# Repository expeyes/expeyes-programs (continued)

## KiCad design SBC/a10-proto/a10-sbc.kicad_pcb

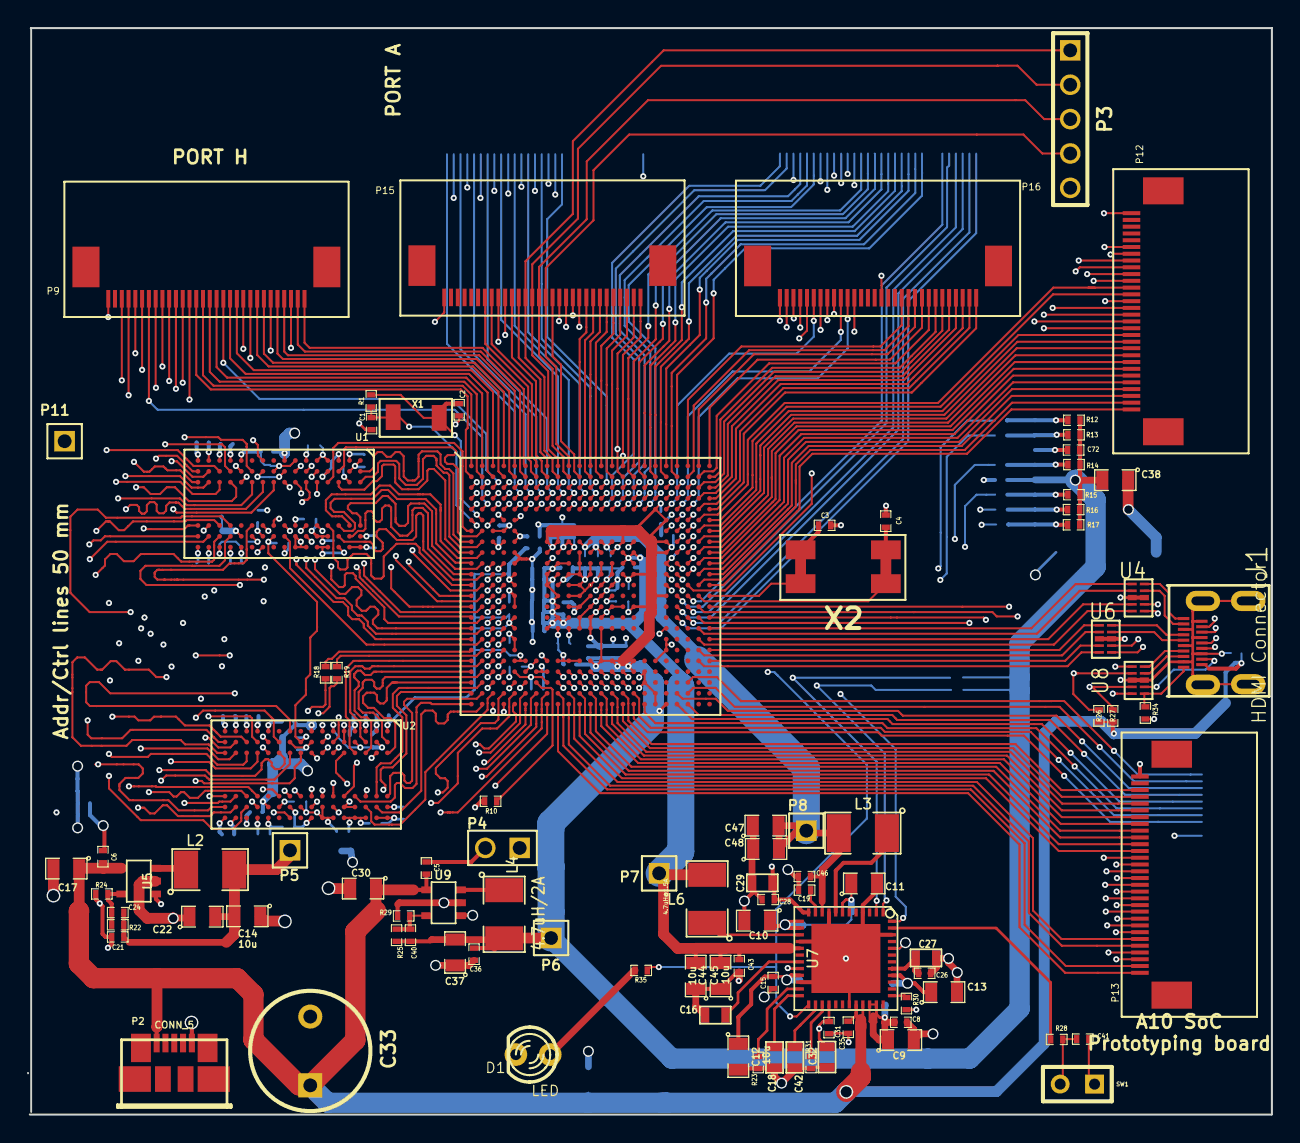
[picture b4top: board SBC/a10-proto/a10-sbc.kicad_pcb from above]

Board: 6 copper layers, 91.8 x 80.3 mm, 180 parts (0 on the bottom side), 331 nets.

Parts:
C1, C2, C3, C4: 18pF; SM0402
C5, C6, C24, C40: 22pF; SM0402
C7, C8, C15, C19, C21, C23, C26, C28, C31, C35, C36, C41, C43, C46, C49, C50, C51, C52, C53, C54, C55, C56, C57, C58, C59, C60, C61, C62, C63, C64, C65, C66, C67, C68, C69, C70, C71, C72, C73, C74, C75, C76, C77, C78, C79, C80, C81, C82, C83, C84, C85, C86, C87, C88, C89, C90, C91, C92, C93, C94, C95, C96, C97, C98, C99, C100, C101, C102, C103, C104, C105, C106, C107, C109, C110, C111, C112: .22u; SM0402
C9, C10, C11, C12, C13, C14, C17, C22, C30, C34, C37, C38, C44, C45, C47, C48: 10u; SM0805
C16, C18, C42: 1uF; SM0603
C20, C27, C29: 4.7u; SM0603
C32: 1u; SM0603
C33: 220u; C2V8
C108: 22u; SM0402
D1: LED; LED-3MM
J1: HDMI Connector; HDMI
J5: USD; microsd_socket
L2: 4.7uH/3A; SM1210L
L3, L6: 4.7uH@1.5A; SM1210L
L4: 4.7uH/2A; SM1210L
P1, P9, P10, P12, P13, P15, P16: C30; FPC30-0.5mm
P2: CONN_5; conn_usb_B_micro_smd
P3: CONN_5; PIN_ARRAY_5x1
P4: UBOOT; PIN_ARRAY_2X1
P5, P6, P7, P8, P11: CONN_1; PIN_ARRAY_1
P14: CONN_10; FPC10-0.5mm
R1: 10M; SM0402
R2: 5k1; SM0402
R3, R5, R6, R7, R8, R9, R28: 33; SM0402
R4, R10, R11, R30: 240; SM0402
R12, R13, R14, R15, R16, R17: 47K; SM0402
R18, R19: 22; SM0402
R20, R21, R26, R27, R31, R32, R33: 2k2; SM0402
R22, R25: 15k; SM0402
R23: 200k; SM0402
R24: 10k; SM0402
R29: 3.3k; SM0402
R34: 47k; SM0402
R35: 4k7; SM0402
SW1: SW_PUSH; SIL-2
U1, U2: 4GBDDR3; FBGA96-new
U3: A10-SOC; TFBGA441-new
U4, U6, U8: 524P; RCLAMP
U5, U9: SY8008C; SOT23-5
U7: AXP209; QFN48+1
X1: 32.768k; crystal-32k-4.5x1.9mm
X2: 24MHz; Crystal_SMD_7x5mm

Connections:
1.2V: C43.1, C44.2, C45.2, C49.1, C50.1, C51.1, C52.1, C53.1, C54.1, C55.1, C56.1, L6.2, P7.1, U3.J15, U3.J16, U3.K9, U3.K10, U3.K15, U3.K16, U3.L8, U3.L9, U3.M8, U3.N9, U3.P9, U3.R9, U3.R10, U3.T8, U7.17
1.25V: C46.1, C47.2, C48.2, C57.1, C58.1, C59.1, L3.2, P8.1, U3.H11, U3.H12, U3.H13, U3.H14, U3.J12, U3.J13, U7.10
3.3V: C7.2, C36.2, C37.2, C38.2, C40.2, C60.1, C61.1, C62.1, C63.1, C64.1, C65.1, C66.1, C67.1, C68.1, C69.1, C70.1, C71.1, C72.1, J5.4, L4.2, P6.1, R12.1, R13.1, R14.1, R15.1, R16.1, R17.1, R20.1, R21.1, R25.2, U3.AC19, U3.E18, U3.F19, U3.H8, U3.H9, U3.H10, U3.H15, U3.H19, U3.J8, U3.J9, U3.J10, U3.J14, U3.J19, U3.L15, U3.L16, U3.N19, U3.P16, U3.T13, U3.W12, U3.W13, U3.W14, U3.W15, U3.W16, U3.Y16
5V_IN: C5.2, C6.2, C17.1, C23.2, C30.1, C33.1, C34.1, C35.2, J1.18, P2.1, R26.1, R27.1, U5.4, U7.32, U7.33, U9.4
/BA0: U1.M2, U2.M2, U3.K3
/BA1: U1.N8, U2.N8, U3.L4
/BA2: U1.M3, U2.M3, U3.K4
/CK: R18.1, U1.J7, U2.J7
/CK#: R19.1, U1.K7, U2.K7
/CKE: U1.K9, U2.K9, U3.N3
/CS#: U1.L2, U2.L2, U3.V3
/DQ0: U2.E3, U3.AB4
/DQ1: U2.F7, U3.AC8
/DQ2: U2.F2, U3.AC4
/DQ3: U2.F8, U3.AB8
/DQ4: U2.H7, U3.AC7
/DQ5: U2.H8, U3.AB5
/DQ6: U2.H3, U3.AB7
/DQ7: U2.G2, U3.AC3
/DQ8: U2.A7, U3.AB2
/DQ9: U2.C3, U3.Y1
/DQ10: U2.B8, U3.AC2
/DQ11: U2.A2, U3.Y2
/DQ12: U2.A3, U3.AA1
/DQ13: U2.C8, U3.AB3
/DQ14: U2.C2, U3.W2
/DQ15: U2.D7, U3.AC1
/DQ16: U1.F2, U3.N1
/DQ17: U1.F7, U3.T2
/DQ18: U1.H3, U3.N2
/DQ19: U1.H7, U3.U1
/DQ20: U1.H8, U3.U2
/DQ21: U1.E3, U3.P1
/DQ22: U1.F8, U3.T1
/DQ23: U1.G2, U3.M2
/DQ24: U1.B8, U3.L1
/DQ25: U1.A2, U3.H1
/DQ26: U1.C8, U3.L2
/DQ27: U1.A3, U3.H2
/DQ28: U1.C3, U3.J1
/DQ29: U1.D7, U3.M1
/DQ30: U1.C2, U3.G2
/DQ31: U1.A7, U3.K2
/EXTEN: U7.20, U9.1
/LCLK: P13.4, U3.Y9
/LD0: P13.28, U3.AB15
/LD1: P13.27, U3.AC15
/LD2: P13.26, U3.AB14
/LD3: P13.25, U3.AC14
/LD4: P13.24, U3.AB13
/LD5: P13.23, U3.AC13
/LD6: P13.22, U3.AB12
/LD7: P13.21, U3.AC12
/LD8: P13.20, U3.AB11
/LD9: P13.19, U3.AC11
/LD10: P13.18, U3.Y15
/LD11: P13.17, U3.AA15
/LD12: P13.16, U3.Y14
/LD13: P13.15, U3.AA14
/LD14: P13.14, U3.Y13
/LD15: P13.13, U3.AA13
/LD16: P13.12, U3.Y12
/LD17: P13.11, U3.AA12
/LD18: P13.10, U3.Y11
/LD19: P13.9, U3.AA11
/LD20: P13.8, U3.Y10
/LD21: P13.7, U3.AA10
/LD22: P13.6, U3.AB10
/LD23: P13.5, U3.AC10
/LDE: P13.3, U3.AA9
/LHSYN: P13.2, U3.AB9
/LIN_L: P14.3, U3.AB20
/LIN_R: P14.2, U3.AB21
/LVSYN: P13.1, U3.AC9
/MICIN1: P14.5, U3.AC20
/MICIN2: P14.4, U3.AC21
/NMI#: U3.F5, U7.48
/ODT: U1.K1, U2.K1, U3.AA5
/PA0: P1.1, U3.D5
/PA1: P1.2, U3.E5
/PA2: P1.3, U3.D6
/PA3: P1.4, U3.E6
/PA4: P1.5, U3.D7
/PA5: P1.6, U3.E7
/PA6: P1.7, U3.D8
/PA7: P1.8, U3.E8
/PA8: P1.9, U3.D9
/PA9: P1.10, U3.E9
/PA10: P1.11, U3.D10
/PA11: P1.12, U3.E10
/PA12: P1.13, U3.D11
/PA13: P1.14, U3.E11
/PA14: P1.15, U3.D12
/PA15: P1.16, U3.E12
/PA16: P1.17, U3.D13
/PA17: P1.18, U3.C13
/PB2: P15.3, U3.A14
/PB3: P15.4, U3.B14
/PB4: P15.5, U3.A13
/PB5: P15.6, U3.B13
/PB6: P15.7, U3.A12
/PB7: P15.8, U3.B12
/PB8: P15.9, U3.A11
/PB9: P15.10, U3.C12
/PB10: P15.11, U3.C11
/PB11: P15.12, U3.C10
/PB12: P15.13, U3.C9
/PB13: P15.14, U3.B11
/PB14/JMS: P3.4, P15.15, U3.A10
/PB15/JCK: P3.3, P15.16, U3.B10
/PB16/JD0: P3.2, P15.17, U3.A9
/PB17/JDI: P3.1, P15.18, U3.B9
/PB18: P15.19, U3.A8
/PB19: P15.20, U3.B8
/PB20: P15.21, U3.C8
/PB21: P15.22, U3.C7
/PC0: P12.1, U3.M23
/PC1: P12.2, U3.M22
/PC2: P12.3, U3.L23
/PC3: P12.4, U3.L22
/PC4: P12.5, U3.K23
/PC5: P12.6, U3.K22
/PC6: P12.7, U3.J23
/PC7: P12.8, U3.J22
/PC8: P12.9, U3.H23
/PC9: P12.10, U3.H22
/PC10: P12.11, U3.G23
/PC11: P12.12, U3.G22
/PC12: P12.13, U3.H21
/PC13: P12.14, U3.H20
/PC14: P12.15, U3.G21
/PC15: P12.16, U3.G20
/PC16: P12.17, U3.M21
/PC17: P12.18, U3.F23
/PC18: P12.19, U3.F22
/PC19: P12.20, U3.L21
/PC20: P12.21, U3.K21
/PC21: P12.22, U3.J21
/PC22: P12.23, U3.J20
/PC23: P12.24, U3.G19
/PC24: P12.25, U3.F21
/PE0: P16.1, U3.E23
/PE1: P16.2, U3.E22
/PE2: P16.3, U3.D23
/PE3: P16.4, U3.D22
/PE4: P16.5, U3.C23
/PE5: P16.6, U3.C22
/PE6: P16.7, U3.B23
/PE7: P16.8, U3.B22
/PE8: P16.9, U3.A23
/PE9: P16.10, U3.A22
/PE10: P16.11, U3.B21
/PE11: P16.12, U3.A21
/PG0: P16.19, U3.F20
/PG1: P16.20, U3.E21
/PG2: P16.21, U3.E20
/PG3: P16.22, U3.D21
/PG4: P16.23, U3.D20
/PG5: P16.24, U3.C21
/PG6: P16.25, U3.E19
/PG7: P16.26, U3.C20
/PG8: P16.27, U3.D19
/PG9: P16.28, U3.C19
/PG10: P16.29, U3.D18
/PG11: P16.30, U3.C18
/PH0: P9.1, U3.A6
/PH1: P9.2, U3.B6
/PH2: P9.3, U3.C6
/PH3: P9.4, U3.A5
/PH4: P9.5, U3.B5
/PH5: P9.6, U3.C5
/PH6: P9.7, U3.A4
/PH7: P9.8, U3.B4
/PH8: P9.9, U3.C4
/PH9: P9.10, U3.D4
/PH10: P9.11, U3.A3
/PH11: P9.12, U3.B3
/PH12: P9.13, U3.C3
/PH13: P9.14, U3.A2
/PH14: P9.15, U3.B2
/PH15: P9.16, U3.A1
/PH16: P9.17, U3.B1
/PH17: P9.18, U3.C1
/PH18: P9.19, U3.C2
/PH19: P9.20, U3.D1
/PH20: P9.21, U3.D2
/PH21: P9.22, U3.D3
/PH22: P9.23, U3.E1
/PH23: P9.24, U3.E2
/PH24: P9.25, U3.E3
/PH25: P9.26, U3.E4
/PH26: P9.27, U3.F3
/PH27: P9.28, U3.F4
/PI0: P10.22, U3.A20
/PI1: P10.21, U3.B20
/PI2: P10.20, U3.A19
/PI3: P10.19, U3.B19
/PI4: P10.18, U3.A18
/PI5: P10.17, U3.B18
/PI6: P10.16, U3.A17
/PI7: P10.15, U3.B17
/PI8: P10.14, U3.A16
/PI9: P10.13, U3.B16
/PI10: P10.12, U3.C17
/PI11: P10.11, U3.D17
/PI12: P10.10, U3.C16
/PI13: P10.9, U3.D16
/PI14: P10.8, U3.C15
/PI15: P10.7, U3.D15
/PI16: P10.6, U3.E17
/PI17: P10.5, U3.E16
/PI18: P10.4, U3.E15
/PI19: P10.3, U3.D14
/PI20: P10.2, U3.E14
/PI21: P10.1, U3.E13
/RESET#: R35.1, U3.C14, U7.25
/SA0: U1.N3, U2.N3, U3.W4
/SA1: U1.P7, U2.P7, U3.R4
/SA2: U1.P3, U2.P3, U3.U4
/SA3: U1.N2, U2.N2, U3.M4
/SA4: U1.P8, U2.P8, U3.Y4
/SA5: U1.P2, U2.P2, U3.N4
/SA6: U1.R8, U2.R8, U3.V4
/SA7: U1.R2, U2.R2, U3.M3
/SA8: U1.T8, U2.T8, U3.AA3
/SA9: U1.R3, U2.R3, U3.P4
/SA10: U1.L7, U2.L7, U3.L3
/SA11: U1.R7, U2.R7, U3.W3
/SA12: U1.N7, U2.N7, U3.P3
/SA13: U1.T3, U2.T3, U3.Y3
/SA14: U1.T7, U2.T7, U3.R3
/SCAS: U1.K3, U2.K3, U3.U3
/SCK: R18.2, U3.V1
/SCK#: R19.2, U3.V2
/SDQM0: U2.E7, U3.AC6
/SDQM1: U2.D3, U3.W1
/SDQM2: U1.E7, U3.R2
/SDQM3: U1.D3, U3.G1
/SDQS0: U2.F3, U3.AB6
/SDQS0#: U2.G3, U3.AC5
/SDQS1: U2.C7, U3.AB1
/SDQS1#: U2.B7, U3.AA2
/SDQS2: U1.F3, U3.R1
/SDQS2#: U1.G3, U3.P2
/SDQS3: U1.C7, U3.K1
/SDQS3#: U1.B7, U3.J2
/SRAS: U1.J3, U2.J3, U3.T4
/SRST: U1.T2, U2.T2, U3.AA6
/SWE: U1.L3, U2.L3, U3.T3
/TWI0SCK: P15.1, R20.2, U3.A15, U7.2
/TWI0SDA: P15.2, R21.2, U3.B15, U7.1
/U0Rx/23: P15.24, U3.B7
/U0Tx/22: P15.23, U3.A7
/USB0M: P10.26, U3.N20
/USB0P: P10.25, U3.N21
/USB1M: P10.28, U3.P20
/USB1P: P10.27, U3.P21
/USB2M: P10.30, U3.R20
/USB2P: P10.29, U3.R21
/VGA_B: P14.7, U3.AB16
/VGA_G: P14.8, U3.AC16
/VGA_R: P14.6, U3.AC17
/VMIC: P14.1, U3.AA21
AVCC: C28.2, C29.2, U3.T19, U5.1, U7.12
DRAM_REF: C73.1, C74.1, C75.1, C76.1, C77.1, C78.1, C79.1, C80.1, C81.1, P11.1, R32.1, R33.1, U1.H1, U1.M8, U2.H1, U2.M8, U3.AA8, U3.H3, U3.H4, U3.Y5
DRAM_VCC: C14.2, C20.2, C21.2, C22.2, C24.2, C81.2, C82.1, C83.1, C84.1, C85.1, C86.1, C87.1, C88.1, C89.1, C90.1, C91.1, C92.1, C93.1, C94.1, C95.1, C96.1, C97.1, C98.1, C99.1, C100.1, C101.1, C102.1, C103.1, C104.1, C105.1, C106.1, C107.1, C108.2, C109.1, C110.1, C111.1, C112.1, L2.2, P5.1, R22.2, R33.2, U1.A1, U1.A8, U1.B2, U1.C1, U1.C9, U1.D2, U1.D9, U1.E9, U1.F1, U1.G7, U1.H2, U1.H9, U1.K2, U1.K8, U1.N1, U1.N9, U1.R1, U1.R9, U2.A1, U2.A8, U2.B2, U2.C1, U2.C9, U2.D2, U2.D9, U2.E9, U2.F1, U2.G7, U2.H2, U2.H9, U2.K2, U2.K8, U2.N1, U2.N9, U2.R1, U2.R9, U3.G5, U3.H5, U3.L5, U3.M5, U3.R5, U3.T5, U3.W5, U3.W6, U3.W7, U3.Y6
GND: C1.2, C2.2, C3.2, C4.2, C5.1, C6.1, C7.1, C8.2, C9.2, C10.2, C11.2, C12.2, C13.2, C14.1, C15.2, C16.1, C17.2, C18.1, C19.2, C20.1, C21.1, C22.1, C23.1, C26.1, C27.1, C28.1, C29.1, C30.2, C31.1, C32.1, C33.2, C34.2, C35.1, C36.1, C37.1, C38.1, C41.1, C42.1, C43.2, C44.1, C45.1, C46.2, C47.1, C48.1, C49.2, C50.2, C51.2, C52.2, C53.2, C54.2, C55.2, C56.2, C57.2, C58.2, C59.2, C60.2, C61.2, C62.2, C63.2, C64.2, C65.2, C66.2, C67.2, C68.2, C69.2, C70.2, C71.2, C72.2, C73.2, C74.2, C75.2, C76.2, C77.2, C78.2, C79.2, C80.2, C82.2, C83.2, C84.2, C85.2, C86.2, C87.2, C88.2, C89.2, C90.2, C91.2, C92.2, C93.2, C94.2, C95.2, C96.2, C97.2, C98.2, C99.2, C100.2, C101.2, C102.2, C103.2, C104.2, C105.2, C106.2, C107.2, C108.1, C109.2, C110.2, C111.2, C112.2, D1.2, J1.2, J1.5, J1.8, J1.11, J1.14, J1.17, J1.sh1, J1.sh2, J1.sh3, J1.sh4, J5.6, J5.sh1, J5.sh2, P1.30, P2.5, P3.5, P4.2, P9.30, P12.30, P13.30, P14.10, P15.30, P16.15, R2.2, R4.1, R10.2, R11.2, R23.1, R24.1, R29.1, R30.2, R31.2, R32.2, R34.1, SW1.1, U1.A9, U1.B1, U1.B3, U1.B9, U1.D1, U1.D8, U1.E1, U1.E2, U1.E8, U1.F9, U1.G1, U1.G8, U1.G9, U1.J2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
HCEC: U3.P23, U8.1
HHPD: U3.P22, U8.5
HSCL: R26.2, U3.R23, U8.2
HSDA: R27.2, U3.R22, U8.4
HTX0N: U3.V22, U6.2
HTX0P: U3.V23, U6.1
HTX1N: U3.U22, U4.5
HTX1P: U3.U23, U4.4
HTX2N: U3.T22, U4.2
HTX2P: U3.T23, U4.1
HTXCN: U3.W22, U6.5
HTXCP: U3.W23, U6.4
IPSOUT: C8.1, C9.1, C10.1, C11.1, C12.1, C13.1, C15.1, U7.7, U7.13, U7.14, U7.21, U7.34, U7.35, U7.40, U7.44
LDO1: C31.2, C32.2, U3.K8, U7.28
LDO3: C26.2, C27.2, U7.41
LDO4: C19.1, U7.11
unnamed: R9.2, U3.M20
unnamed: L3.1, U7.8
unnamed: L6.1, U7.15
unnamed: P4.1, U3.W8
unnamed: C40.1, R25.1, R29.2, U9.5
unnamed: C24.1, R22.1, R24.2, U5.5
unnamed: C16.2, U7.19
unnamed: R23.2, U7.23
unnamed: R28.2, U7.47
unnamed: R4.2, U2.L8
unnamed: C18.2, U7.24
unnamed: J5.1, R3.1, R17.2
unnamed: J5.2, R5.1, R16.2
unnamed: R30.1, U7.37
unnamed: C42.2, U7.26
unnamed: C41.2, R28.1, SW1.2
unnamed: R3.2, U3.K19
unnamed: R5.2, U3.K20
unnamed: R6.2, U3.L19
unnamed: R7.2, U3.L20
unnamed: R8.2, U3.M19
unnamed: J5.8, R9.1, R12.2
unnamed: J5.7, R8.1, R13.2
unnamed: J5.5, R7.1, R14.2
unnamed: J5.3, R6.1, R15.2
unnamed: C2.1, R1.2, U3.F2, X1.1
unnamed: R11.1, U1.L8
unnamed: R31.1, U7.27
unnamed: L2.1, U5.3
unnamed: L4.1, U9.3
unnamed: R10.1, U3.AA7
unnamed: R2.1, U3.T10
unnamed: C4.1, U3.N22, X2.1
unnamed: C3.1, U3.N23, X2.2
unnamed: D1.1, R35.2
unnamed: C1.1, R1.1, U3.F1, X1.2
unnamed: J1.7, U6.10
unnamed: J1.9, U6.9
unnamed: J1.10, U6.7
unnamed: J1.12, U6.6
unnamed: J1.13, U8.10
unnamed: J1.15, U8.9
unnamed: J1.16, U8.7
unnamed: J1.19, R34.2, U8.6
unnamed: J1.4, U4.7
unnamed: J1.1, U4.10
unnamed: J1.3, U4.9
unnamed: J1.6, U4.6

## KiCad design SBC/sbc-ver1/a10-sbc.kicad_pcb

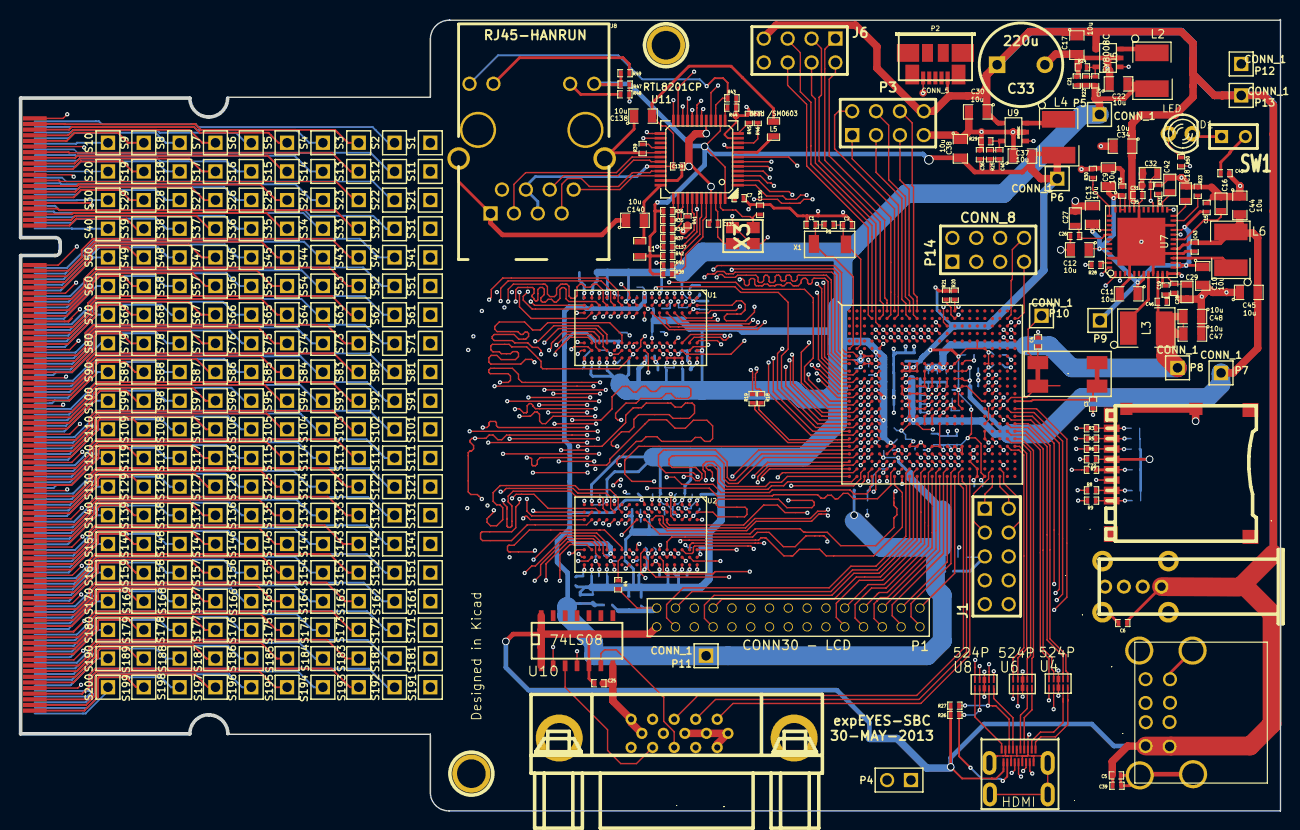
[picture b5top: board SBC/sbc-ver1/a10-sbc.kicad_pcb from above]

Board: 6 copper layers, 134.0 x 84.2 mm, 426 parts (0 on the bottom side), 459 nets.

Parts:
C1, C2, C3, C4, C135, C136: 18pF; SM0402
C5, C6, C24, C40: 22pF; SM0402
C7, C8, C15, C19, C21, C23, C26, C28, C31, C35, C36, C39, C41, C43, C46, C49, C50, C51, C52, C53, C54, C55, C56, C57, C58, C59, C60, C61, C62, C63, C64, C65, C66, C67, C68, C69, C70, C71, C72, C73, C74, C75, C76, C77, C78, C79, C80, C81, C82, C83, C84, C85, C86, C87, C88, C89, C90, C91, C92, C93, C94, C95, C96, C97, C98, C99, C100, C101, C102, C103, C104, C105, C106, C107, C109, C110, C111, C112, C113, C114, C115, C116, C117, C118, C119, C120, C121, C122, C123, C124, C125, C137, C139: .22u; SM0402
C9, C10, C11, C12, C13, C14, C17, C22, C30, C34, C37, C38, C44, C45, C47, C48, C138, C140: 10u; SM0805
C16, C18, C42: 1uF; SM0603
C20, C27, C29: 4.7u; SM0603
C25: .22; SM0402
C32: 1u; SM0603
C33: 220u; C2V8
C108: 22u; SM0402
D1: LED; LED-3MM
J1: CONN10; PIN_ARRAY_5x2
J2: DB15; DB_15F-VGA
J3: DUSB; USB_Double-from-FCI
J4: USB1; conn_usb_A-vert
J5: USD; microsd_socket
J6: CONN_8; pin_array_4x2
J7: HDMI
J8: RJ45-HANRUN
L1: Bead / SM0603; SM0603_Capa
L2: 4.7uH/3A; SM1812E
L3, L6: 4.7uH@1.5A; SM1812E
L4: 4.7uH/2A; SM1812E
L5: bead /SM0603; SM0603_Capa
P1: CONN30 - LCD; pin2mm-30
P2: CONN_5; conn_usb_B_micro_smd
P3, P14: CONN_8; pin_array_4x2
P4: UBOOT; PIN_ARRAY_2X1
P5, P6, P7, P8, P9, P10, P11, P12, P13: CONN_1; PIN_ARRAY_1
R1: 10M; SM0402
R2, R34, R35, R36, R37, R38, R40, R41, R42, R43, R44, R45, R46, R47: 5k1; SM0402
R3, R5, R6, R7, R8, R9, R28: 33; SM0402
R4, R10, R11, R30: 240; SM0402
R12, R13, R14, R15, R16, R17: 47K; SM0402
R18, R19: 22; SM0402
R20, R21, R26, R27, R31, R32, R33, R39: 2k2; SM0402
R22, R25: 15k; SM0402
R23: 200k; SM0402
R24: 10k; SM0402
R29: 3.3k; SM0402
R48, R49: 1k; SM0402
R50: 4k7; SM0402
S1, S2, S3, S4, S5, S6, S7, S8, S9, S10, S11, S12, S13, S14, S15, S16, S17, S18, S19, S20, S21, S22, S23, S24, S25, S26, S27, S28, S29, S30, S31, S32, S33, S34, S35, S36, S37, S38, S39, S40, S41, S42, S43, S44, S45, S46, S47, S48, S49, S50, S51, S52, S53, S54, S55, S56, S57, S58, S59, S60, S61, S62, S63, S64, S65, S66, S67, S68, S69, S70, S71, S72, S73, S74, S75, S76, S77, S78, S79, S80, S81, S82, S83, S84, S85, S86, S87, S88, S89, S90, S91, S92, S93, S94, S95, S96, S97, S98, S99, S100, S101, S102, S103, S104, S105, S106, S107, S108, S109, S110, S111, S112, S113, S114, S115, S116, S117, S118, S119, S120, S121, S122, S123, S124, S125, S126, S127, S128, S129, S130, S131, S132, S133, S134, S135, S136, S137, S138, S139, S140, S141, S142, S143, S144, S145, S146, S147, S148, S149, S150, S151, S152, S153, S154, S155, S156, S157, S158, S159, S160, S161, S162, S163, S164, S165, S166, S167, S168, S169, S170, S171, S172, S173, S174, S175, S176, S177, S178, S179, S180, S181, S182, S183, S184, S185, S186, S187, S188, S189, S190, S191, S192, S193, S194, S195, S196, S197, S198, S199, S200: P; PIN_CPU_PAD1
SO1: SODIMM200_EDGE_D; m-pad-2.1-SODIMM200-JAE
SW1: SW_PUSH; SIL-2
U1, U2: 4GBDDR3; FBGA96-new
U3: A10-SOC; TFBGA441-new
U4, U6, U8: 524P; RCLAMP
U5, U9: SY8008C; SOT23-5
U7: AXP209; QFN48+1
U10: 74LS08; SO14E
U11: RTL8201CP; lqfp48
X1: 32k; crystal-32k-4.5x1.9mm
X2: 24M; Crystal_SMD_7x5mm
X3: 25M; Crystal-TXC-SMD3.2x2.5

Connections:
1.2V: C43.1, C44.2, C45.2, C49.1, C50.1, C51.1, C52.1, C53.1, C54.1, C55.1, C56.1, C57.1, L6.2, P7.1, U3.J15, U3.J16, U3.K9, U3.K10, U3.K15, U3.K16, U3.L8, U3.L9, U3.M8, U3.N9, U3.P9, U3.R9, U3.R10, U3.T8, U7.17
1.25V: C46.1, C47.2, C48.2, C58.1, C59.1, C60.1, L3.2, P8.1, U3.H11, U3.H12, U3.H13, U3.H14, U3.J12, U3.J13, U7.10
3.3V: C7.2, C36.2, C37.2, C38.2, C40.2, C61.1, C62.1, C63.1, C64.1, C65.1, C66.1, C67.1, C68.1, C69.1, C70.1, C71.1, C72.1, J5.4, J8.9, L1.1, L4.2, P6.1, R12.1, R13.1, R14.1, R15.1, R16.1, R17.1, R20.1, R21.1, R25.2, R34.2, R35.2, R36.2, R37.2, R38.2, R42.1, R47.2, R49.1, U3.AC19, U3.E18, U3.F19, U3.H8, U3.H9, U3.H10, U3.H15, U3.H19, U3.J8, U3.J9, U3.J10, U3.J14, U3.J19, U3.L15, U3.L16, U3.N19, U3.P16, U3.T13, U3.W12, U3.W13, U3.W14, U3.W15, U3.W16, U3.Y16, U11.14, U11.48
5V_IN: C5.2, C6.2, C17.1, C25.2, C30.1, C33.1, C34.1, C35.2, C39.2, J3.1, J3.2, J4.1, J6.7, J7.18, P1.29, P2.1, P3.8, P13.1, R26.1, R27.1, U5.4, U7.32, U7.33, U9.4, U10.1, U10.5, U10.14
/BA0: U1.M2, U2.M2, U3.K3
/BA1: U1.N8, U2.N8, U3.L4
/BA2: U1.M3, U2.M3, U3.K4
/CK: R18.1, U1.J7, U2.J7
/CK#: R19.1, U1.K7, U2.K7
/CKE: U1.K9, U2.K9, U3.N3
/CS#: U1.L2, U2.L2, U3.V3
/DQ0: U2.E3, U3.AB4
/DQ1: U2.F7, U3.AC7
/DQ2: U2.F2, U3.AC4
/DQ3: U2.F8, U3.AB8
/DQ4: U2.H3, U3.AC8
/DQ5: U2.H8, U3.AB5
/DQ6: U2.G2, U3.AB7
/DQ7: U2.H7, U3.AC3
/DQ8: U2.D7, U3.AB2
/DQ9: U2.C3, U3.Y1
/DQ10: U2.C8, U3.AC2
/DQ11: U2.C2, U3.Y2
/DQ12: U2.A7, U3.AA1
/DQ13: U2.A2, U3.AB3
/DQ14: U2.B8, U3.W2
/DQ15: U2.A3, U3.AC1
/DQ16: U1.E3, U3.N1
/DQ17: U1.F7, U3.T2
/DQ18: U1.F2, U3.N2
/DQ19: U1.F8, U3.U1
/DQ20: U1.H3, U3.U2
/DQ21: U1.H8, U3.P1
/DQ22: U1.G2, U3.T1
/DQ23: U1.H7, U3.M2
/DQ24: U1.D7, U3.L1
/DQ25: U1.C3, U3.H1
/DQ26: U1.C8, U3.L2
/DQ27: U1.C2, U3.H2
/DQ28: U1.A7, U3.J1
/DQ29: U1.A2, U3.M1
/DQ30: U1.B8, U3.G2
/DQ31: U1.A3, U3.K2
/EXTEN: U7.20, U9.1
/HCEC: U3.P23, U8.1
/HHPD: U3.P22, U8.5
/HSCL: U3.R23, U8.2
/HSDA: U3.R22, U8.4
/HTX0N: U3.V22, U6.2
/HTX0P: U3.V23, U6.1
/HTX1N: U3.U22, U4.5
/HTX1P: U3.U23, U4.4
/HTX2N: U3.T22, U4.2
/HTX2P: U3.T23, U4.1
/HTXCN: U3.W22, U6.5
/HTXCP: U3.W23, U6.4
/J_CK0: P3.5, U3.B10
/J_DI0: P3.3, U3.B9
/J_DO0: P3.4, U3.A9
/J_MS0: P3.6, U3.A10
/LCLK: P1.25, U3.Y9
/LD0: P1.1, U3.AB15
/LD1: P1.2, U3.AC15
/LD2: P1.3, U3.AB14
/LD3: P1.4, U3.AC14
/LD4: P1.5, U3.AB13
/LD5: P1.6, U3.AC13
/LD6: P1.7, U3.AB12
/LD7: P1.8, U3.AC12
/LD8: P1.9, U3.AB11
/LD9: P1.10, U3.AC11
/LD10: P1.11, U3.Y15
/LD11: P1.12, U3.AA15
/LD12: P1.13, U3.Y14
/LD13: P1.14, U3.AA14
/LD14: P1.15, U3.Y13
/LD15: P1.16, U3.AA13
/LD16: P1.17, U3.Y12
/LD17: P1.18, U3.AA12
/LD18: P1.19, U3.Y11
/LD19: P1.20, U3.AA11
/LD20: P1.21, U3.Y10
/LD21: P1.22, U3.AA10
/LD22: P1.23, U3.AB10
/LD23: P1.24, U3.AC10
/LDE: P1.26, U3.AA9
/LHSYN: P1.27, U3.AB9, U10.4
/LIN_L: J1.3, U3.AB20
/LIN_R: J1.4, U3.AB21
/LVSYN: P1.28, U3.AC9, U10.2
/MICIN1: J1.1, U3.AC20
/MICIN2: J1.2, U3.AC21
/NMI#: U3.F5, U7.48
/ODT: U1.K1, U2.K1, U3.AA5
/PE0: P14.1, U3.E23
/PE1: P14.2, U3.E22
/PE2: P14.3, U3.D23
/PE3: P14.4, U3.D22
/PE4: P14.5, U3.C23
/PE5: P14.6, U3.C22
/PE6: P14.7, U3.B23
/PE7: P14.8, U3.B22
/RESET#: R50.1, U3.C14, U7.25
/SA0: U1.N3, U2.N3, U3.W4
/SA1: U1.P7, U2.P7, U3.R4
/SA2: U1.P3, U2.P3, U3.U4
/SA3: U1.N2, U2.N2, U3.M4
/SA4: U1.P8, U2.P8, U3.Y4
/SA5: U1.P2, U2.P2, U3.N4
/SA6: U1.R8, U2.R8, U3.V4
/SA7: U1.R2, U2.R2, U3.M3
/SA8: U1.T8, U2.T8, U3.AA3
/SA9: U1.R3, U2.R3, U3.P4
/SA10: U1.L7, U2.L7, U3.L3
/SA11: U1.R7, U2.R7, U3.W3
/SA12: U1.N7, U2.N7, U3.P3
/SA13: U1.T3, U2.T3, U3.Y3
/SA14: U1.T7, U2.T7, U3.R3
/SCAS: U1.K3, U2.K3, U3.U3
/SCK: R18.2, U3.V1
/SCK#: R19.2, U3.V2
/SDQM0: U2.E7, U3.AC6
/SDQM1: U2.D3, U3.W1
/SDQM2: U1.E7, U3.R2
/SDQM3: U1.D3, U3.G1
/SDQS0: U2.F3, U3.AB6
/SDQS0#: U2.G3, U3.AC5
/SDQS1: U2.C7, U3.AB1
/SDQS1#: U2.B7, U3.AA2
/SDQS2: U1.F3, U3.R1
/SDQS2#: U1.G3, U3.P2
/SDQS3: U1.C7, U3.K1
/SDQS3#: U1.B7, U3.J2
/SRAS: U1.J3, U2.J3, U3.T4
/SRST: U1.T2, U2.T2, U3.AA6
/SWE: U1.L3, U2.L3, U3.T3
/TWI0SCK: R20.2, U3.A15, U7.2
/TWI0SDA: R21.2, U3.B15, U7.1
/U0Rx: P3.1, U3.B7
/U0Tx: P3.2, U3.A7
/U3RX: J6.2, U3.B6
/U3TX: J6.1, U3.A6
/U4RX: J6.4, U3.C5
/U4TX: J6.3, U3.B5
/U5RX: J6.6, U3.B4
/U5TX: J6.5, U3.A4
/USB1M: J3.3, U3.P20
/USB1P: J3.5, U3.P21
/USB2M: J3.4, U3.R20
/USB2P: J3.6, U3.R21
/VGA_B: J2.3, U3.AB16
/VGA_G: J2.2, U3.AC16
/VGA_R: J2.1, U3.AC17
/VMIC: J1.6, U3.AA21
/VRA1: J1.7, U3.W20
/VRA2: J1.8, U3.V20
/VRP: J1.9, U3.W21
/ethernet/ETHAVDD: C140.2, L1.2, U11.36
/ethernet/LED0: R47.1, R48.1, U11.9
/ethernet/LED4: J8.12, R43.1, U11.15
/ethernet/PFWBOUT: C138.2, C139.2, J8.4, J8.5, L5.1, U11.32
/ethernet/RX+: J8.3, U11.31
/ethernet/RX-: J8.6, U11.30
/ethernet/TX+: J8.1, U11.34
/ethernet/TX-: J8.2, U11.33
AVCC: C28.2, C29.2, U3.T19, U5.1, U7.12
DRAM_REF: C73.1, C74.1, C75.1, C76.1, C77.1, C78.1, C79.1, C80.1, C81.1, P11.1, R32.1, R33.1, U1.H1, U1.M8, U2.H1, U2.M8, U3.AA8, U3.H3, U3.H4, U3.Y5
DRAM_VCC: C14.2, C20.2, C21.2, C22.2, C23.1, C24.2, C81.2, C82.1, C83.1, C84.1, C85.1, C86.1, C87.1, C88.1, C89.1, C90.1, C91.1, C92.1, C93.1, C94.1, C95.1, C96.1, C97.1, C98.1, C99.1, C100.1, C101.1, C102.1, C103.1, C104.1, C105.1, C106.1, C107.1, C108.2, C109.1, C110.1, C111.1, C112.1, C113.1, C114.1, C115.1, C116.1, C117.1, C118.1, C119.1, C120.1, C121.1, C122.1, C123.1, C124.1, C125.1, L2.2, P5.1, R22.2, R33.2, U1.A1, U1.A8, U1.B2, U1.C1, U1.C9, U1.D2, U1.D9, U1.E9, U1.F1, U1.G7, U1.H2, U1.H9, U1.K2, U1.K8, U1.N1, U1.N9, U1.R1, U1.R9, U2.A1, U2.A8, U2.B2, U2.C1, U2.C9, U2.D2, U2.D9, U2.E9, U2.F1, U2.G7, U2.H2, U2.H9, U2.K2, U2.K8, U2.N1, U2.N9, U2.R1, U2.R9, U3.G5, U3.H5, U3.L5, U3.M5, U3.R5, U3.T5, U3.W5, U3.W6, U3.W7, U3.Y6
ECOL: U3.D13, U11.1
ECRS: U3.E12, U11.23
EMDC: U3.E10, U11.25
EMDIO: U3.D11, U11.26
ERXCK: U3.D9, U11.16
ERXD0: U3.E6, U11.21
ERXD1: U3.D6, U11.20
ERXD2: U3.E5, U11.19
ERXD3: U3.D5, U11.18
ERXDV: U3.D10, U11.22
ERXERR: U3.E9, U11.24
ETXCK: U3.D12, U11.7
ETXD0: U3.E8, U11.6
ETXD1: U3.D8, U11.5
ETXD2: U3.E7, U11.4
ETXD3: U3.D7, U11.3
ETXEN: U3.E11, U11.2
ETXERR: C137.2, R42.2, U3.C13, U11.42
GND: C1.2, C2.2, C3.2, C4.2, C5.1, C6.1, C7.1, C8.2, C9.2, C10.2, C11.2, C12.2, C13.2, C14.1, C15.2, C16.1, C17.2, C18.1, C19.2, C20.1, C21.1, C22.1, C23.2, C25.1, C26.1, C27.1, C28.1, C29.1, C30.2, C31.1, C32.1, C33.2, C34.2, C35.1, C36.1, C37.1, C38.1, C39.1, C41.1, C42.1, C43.2, C44.1, C45.1, C46.2, C47.1, C48.1, C49.2, C50.2, C51.2, C52.2, C53.2, C54.2, C55.2, C56.2, C57.2, C58.2, C59.2, C60.2, C61.2, C62.2, C63.2, C64.2, C65.2, C66.2, C67.2, C68.2, C69.2, C70.2, C71.2, C72.2, C73.2, C74.2, C75.2, C76.2, C77.2, C78.2, C79.2, C80.2, C82.2, C83.2, C84.2, C85.2, C86.2, C87.2, C88.2, C89.2, C90.2, C91.2, C92.2, C93.2, C94.2, C95.2, C96.2, C97.2, C98.2, C99.2, C100.2, C101.2, C102.2, C103.2, C104.2, C105.2, C106.2, C107.2, C108.1, C109.2, C110.2, C111.2, C112.2, C113.2, C114.2, C115.2, C116.2, C117.2, C118.2, C119.2, C120.2, C121.2, C122.2, C123.2, C124.2, C125.2, C135.2, C136.2, C137.1, C138.1, C139.1, C140.1, D1.2, J1.5, J1.10, J2.5, J2.6, J2.7, J2.8, J2.10, J2.11, J3.7, J3.8, J3.sh1, J3.sh2, J3.sh3, J3.sh4, J4.4, J4.5, J4.6, J5.6, J5.sh1, J5.sh2, J6.8, J7.2, J7.5, J7.8, J7.11, J7.14, J7.17, J7.sh1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
IPSOUT: C8.1, C9.1, C10.1, C11.1, C12.1, C13.1, C15.1, P9.1, U7.7, U7.13, U7.14, U7.21, U7.34, U7.35, U7.40, U7.44
LDO1: C31.2, C32.2, U3.K8, U7.28
LDO3: C26.2, C27.2, U7.41
LDO4: C19.1, U7.11
unnamed: R9.2, U3.M20
unnamed: J4.2, U3.N20
unnamed: J4.3, U3.N21
unnamed: J7.6, U4.6
unnamed: J7.1, U4.10
unnamed: J7.3, U4.9
unnamed: J7.4, U4.7
unnamed: J7.7, U6.10
unnamed: J7.9, U6.9
unnamed: J7.10, U6.7
unnamed: J7.12, U6.6
unnamed: L3.1, U7.8
unnamed: L6.1, U7.15
unnamed: R2.1, U3.T10
unnamed: R5.2, U3.K20
unnamed: R7.2, U3.L20
unnamed: R3.2, U3.K19
unnamed: R6.2, U3.L19
unnamed: R8.2, U3.M19
unnamed: P4.1, U3.W8
unnamed: R10.1, U3.AA7
unnamed: S103.1, SO1.103
unnamed: S127.1, SO1.127
unnamed: S125.1, SO1.125
unnamed: S123.1, SO1.123
unnamed: S121.1, SO1.121
unnamed: S119.1, SO1.119
unnamed: S117.1, SO1.117
unnamed: S115.1, SO1.115
unnamed: S113.1, SO1.113
unnamed: S111.1, SO1.111
unnamed: J7.13, U8.10
unnamed: S109.1, SO1.109
unnamed: S107.1, SO1.107
unnamed: S105.1, SO1.105
unnamed: S129.1, SO1.129
unnamed: J7.19, U8.6
unnamed: S101.1, SO1.101
unnamed: J7.16, R27.2, U8.7
unnamed: S99.1, SO1.99
unnamed: J5.1, R3.1, R17.2
unnamed: S97.1, SO1.97
unnamed: J5.7, R8.1, R13.2
unnamed: S95.1, SO1.95
unnamed: J5.5, R7.1, R14.2
unnamed: S93.1, SO1.93
unnamed: J5.8, R9.1, R12.2
unnamed: S91.1, SO1.91
unnamed: J5.3, R6.1, R15.2
unnamed: S89.1, SO1.89
unnamed: J5.2, R5.1, R16.2
unnamed: S87.1, SO1.87
unnamed: J2.14, U10.3
unnamed: S85.1, SO1.85
unnamed: S83.1, SO1.83
unnamed: R30.1, U7.37
unnamed: S81.1, SO1.81
unnamed: C42.2, U7.26
unnamed: S153.1, SO1.153
unnamed: C41.2, R28.1, SW1.2
unnamed: S177.1, SO1.177
unnamed: J2.13, U10.6
unnamed: S175.1, SO1.175
unnamed: C2.1, R1.2, U3.F2, X1.1
unnamed: S173.1, SO1.173
unnamed: S171.1, SO1.171
unnamed: S169.1, SO1.169
unnamed: S167.1, SO1.167
unnamed: S165.1, SO1.165
unnamed: S163.1, SO1.163
unnamed: S161.1, SO1.161
unnamed: S159.1, SO1.159
unnamed: S157.1, SO1.157
unnamed: S155.1, SO1.155
unnamed: S79.1, SO1.79
unnamed: S151.1, SO1.151
unnamed: S149.1, SO1.149
unnamed: S147.1, SO1.147
unnamed: S145.1, SO1.145
unnamed: S143.1, SO1.143
unnamed: S141.1, SO1.141
unnamed: S139.1, SO1.139
unnamed: S137.1, SO1.137
unnamed: S135.1, SO1.135
unnamed: S133.1, SO1.133
unnamed: S131.1, SO1.131
unnamed: S3.1, SO1.3
unnamed: S27.1, SO1.27
unnamed: S25.1, SO1.25
unnamed: D1.1, R50.2
unnamed: S23.1, SO1.23
unnamed: S21.1, SO1.21
unnamed: S19.1, SO1.19
unnamed: S17.1, SO1.17
unnamed: S15.1, SO1.15
unnamed: S13.1, SO1.13
unnamed: S11.1, SO1.11
unnamed: S9.1, SO1.9
unnamed: S7.1, SO1.7
unnamed: S5.1, SO1.5
unnamed: S29.1, SO1.29
unnamed: S1.1, SO1.1
unnamed: S53.1, SO1.53
unnamed: S77.1, SO1.77
unnamed: S75.1, SO1.75
unnamed: S73.1, SO1.73
unnamed: S71.1, SO1.71
unnamed: S69.1, SO1.69
unnamed: S67.1, SO1.67
unnamed: S65.1, SO1.65
unnamed: S63.1, SO1.63
unnamed: S61.1, SO1.61
unnamed: S59.1, SO1.59
unnamed: S57.1, SO1.57
unnamed: S55.1, SO1.55
unnamed: S51.1, SO1.51
unnamed: S49.1, SO1.49
unnamed: S47.1, SO1.47
unnamed: S45.1, SO1.45
unnamed: S43.1, SO1.43
unnamed: S41.1, SO1.41
unnamed: S39.1, SO1.39
unnamed: S37.1, SO1.37
unnamed: S35.1, SO1.35
unnamed: C18.2, U7.24
unnamed: S33.1, SO1.33
unnamed: J7.15, R26.2, U8.9
unnamed: S31.1, SO1.31
unnamed: R4.2, U2.L8
unnamed: C24.1, R22.1, R24.2, U5.5
unnamed: R28.2, U7.47
unnamed: C40.1, R25.1, R29.2, U9.5
unnamed: C16.2, U7.19
unnamed: R23.2, U7.23
unnamed: R31.1, U7.27
unnamed: L2.1, U5.3
unnamed: R11.1, U1.L8
unnamed: L4.1, U9.3
unnamed: C3.1, U3.N23, X2.2
unnamed: C4.1, P10.1, U3.N22, X2.1
unnamed: C1.1, R1.1, U3.F1, X1.2
unnamed: R45.1, U11.12
unnamed: R44.1, U11.13
unnamed: R46.1, U11.10
unnamed: C136.1, U11.47, X3.1
unnamed: L5.2, U11.8
unnamed: J8.10, R48.2
unnamed: J8.11, R49.2
unnamed: R40.1, U11.43
unnamed: R41.1, U11.40
unnamed: R34.1, U11.39
unnamed: R39.1, U11.28
unnamed: C135.1, U11.46, X3.3
unnamed: R35.1, U11.38
unnamed: R36.1, U11.37
unnamed: R37.1, U11.41
unnamed: R38.1, U11.44
unnamed: S179.1, SO1.179
unnamed: S170.1, SO1.170
unnamed: S172.1, SO1.172
unnamed: S174.1, SO1.174
unnamed: S176.1, SO1.176
unnamed: S178.1, SO1.178
unnamed: S180.1, SO1.180
unnamed: S168.1, SO1.168
unnamed: S182.1, SO1.182
unnamed: S181.1, SO1.181
unnamed: S184.1, SO1.184
unnamed: S183.1, SO1.183
unnamed: S186.1, SO1.186
unnamed: S185.1, SO1.185
unnamed: S188.1, SO1.188
unnamed: S187.1, SO1.187
unnamed: S190.1, SO1.190
unnamed: S189.1, SO1.189
unnamed: S192.1, SO1.192
unnamed: S156.1, SO1.156
unnamed: S144.1, SO1.144
unnamed: S146.1, SO1.146
unnamed: S148.1, SO1.148
unnamed: S150.1, SO1.150
unnamed: S152.1, SO1.152
unnamed: S154.1, SO1.154
unnamed: S191.1, SO1.191
unnamed: S158.1, SO1.158
unnamed: S160.1, SO1.160
unnamed: S162.1, SO1.162
unnamed: S164.1, SO1.164
unnamed: S166.1, SO1.166
unnamed: S194.1, SO1.194
unnamed: S193.1, SO1.193
unnamed: S196.1, SO1.196
unnamed: S195.1, SO1.195
unnamed: S198.1, SO1.198
unnamed: S197.1, SO1.197
unnamed: S200.1, SO1.200
unnamed: S199.1, SO1.199
unnamed: S104.1, SO1.104
unnamed: S128.1, SO1.128
unnamed: S126.1, SO1.126
unnamed: S124.1, SO1.124
unnamed: S122.1, SO1.122
unnamed: S120.1, SO1.120
unnamed: S118.1, SO1.118
unnamed: S116.1, SO1.116
unnamed: S114.1, SO1.114
unnamed: S112.1, SO1.112
unnamed: S110.1, SO1.110
unnamed: S108.1, SO1.108
unnamed: S106.1, SO1.106
unnamed: S130.1, SO1.130
unnamed: S102.1, SO1.102
unnamed: S100.1, SO1.100
unnamed: S98.1, SO1.98
unnamed: S96.1, SO1.96
unnamed: S94.1, SO1.94
unnamed: S92.1, SO1.92
unnamed: S90.1, SO1.90
unnamed: S88.1, SO1.88
unnamed: S86.1, SO1.86
unnamed: S84.1, SO1.84
unnamed: S82.1, SO1.82
unnamed: S80.1, SO1.80
unnamed: S142.1, SO1.142
unnamed: S140.1, SO1.140
unnamed: S138.1, SO1.138
unnamed: S136.1, SO1.136
unnamed: S134.1, SO1.134
unnamed: S132.1, SO1.132
unnamed: S4.1, SO1.4
unnamed: S28.1, SO1.28
unnamed: S26.1, SO1.26
unnamed: S24.1, SO1.24
unnamed: S22.1, SO1.22
unnamed: S20.1, SO1.20
unnamed: S18.1, SO1.18
unnamed: S16.1, SO1.16
unnamed: S14.1, SO1.14
unnamed: S12.1, SO1.12
unnamed: S10.1, SO1.10
unnamed: S8.1, SO1.8
unnamed: S6.1, SO1.6
unnamed: S30.1, SO1.30
unnamed: S2.1, SO1.2
unnamed: S54.1, SO1.54
unnamed: S78.1, SO1.78
unnamed: S76.1, SO1.76
unnamed: S74.1, SO1.74
unnamed: S72.1, SO1.72
unnamed: S70.1, SO1.70
unnamed: S68.1, SO1.68
unnamed: S66.1, SO1.66
unnamed: S64.1, SO1.64
unnamed: S62.1, SO1.62
unnamed: S60.1, SO1.60
unnamed: S58.1, SO1.58
unnamed: S56.1, SO1.56
unnamed: S52.1, SO1.52
unnamed: S50.1, SO1.50
unnamed: S48.1, SO1.48
unnamed: S46.1, SO1.46
unnamed: S44.1, SO1.44
unnamed: S42.1, SO1.42
unnamed: S40.1, SO1.40
unnamed: S38.1, SO1.38
unnamed: S36.1, SO1.36
unnamed: S34.1, SO1.34
unnamed: S32.1, SO1.32

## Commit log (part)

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2020-03-08 new symlinks due to prepareHTML
2020-03-08 removed the catch-all target; now all targets must be explicited
2020-03-08 an empty file to mark ml as non-fit for LaTeX
2020-03-08 minimized redundancies
2020-03-08 advances to get the user manuals done
2020-03-08 fixed styles, typos and some other errors in English help files
2020-03-08 adapted the Makefile for making the user manuals
2020-03-10 scopy.py A1-A2 trace removal fixed
2020-03-10 New version of software for ExpEYES Junior is almost complete. It is PyQt5 based, made by modifying ExpEYES-17 code and documentation.
2020-03-11 scope voltage display position fixed
2020-03-11 added SPI support for version 5 and above. added AD9833 support via SPI
2020-03-11 end of a general revision of help files by G.K.
2020-03-11 added localized screenshots eyes17-screen
2020-03-11 fixed a typo in the filename of sound-waves.png
2020-03-11 fixed a typo
2020-03-11 spell-checked French help files
2020-03-12 3.13.rst changed
2020-03-12 tof.ps added
2020-03-12 main.py print removed. tof try: added
2020-03-12 enforced the creation of subdirectories <lang>_sources/_static
2020-03-12 removed extra rst files references
2020-03-12 removed the reference to an obsolete scheme
2020-03-12 replaced an obsoleted scheme
2020-03-12 removed the obsoleted paper format option
2020-03-12 fixed the bug with xcircuit
2020-03-12 copied the python3 version of prepareHTML
2020-03-12 fixed the English Makefile for help files
2020-03-12 fixed a few typos
2020-03-12 added some coherence to permit build of epub books
2020-03-12 added index files for non-English languages
2020-03-13 updated all cover pages and prefaces, enabled the pdflatex build
2020-03-13 prepared a Makefile for Malayalam
2020-03-14 changes to build PDF files with xelatex
2020-03-14 managed to build with xelatex and included files for end users generated by Sphinx
2020-03-14 separated targets to make HTML on one hand, EPUB and PDF user manuals on the other hand
2020-03-14 changed the call to expeyes-junior
2020-03-14 publish the user manual for microhope
2020-03-14 updated ts files
2020-03-14 try to make reproducible builds
2020-03-14 modified Makefiles to manage SOURCE_DATE_EPOCH
2020-03-16 fixed the Malayalam include.tex file
2020-03-16 new Malayalam PDF files, since include.tex was fixed
2020-03-17 now the Spanish translation of the GUI is finished
2020-03-17 fixed the bad sections titles in Malayalam
2020-03-18 fixed reconnect issues in scope. Works with show all voltmeter button properly. shortcut ctrl-r added for reconnect
2020-03-18 reorganised RST files
2020-03-18 updated FR and ES translations
2020-03-18 yet another structure change for the user manual, maybe the last?
2020-03-19 modified the user manual's source structure
2020-03-19 modified the depth of table of contents
2020-03-19 fixed the hierarchy in titles
2020-03-19 improved configuration and make file
2020-03-19 changed the paper size to A4, and the font size to 11pt
2020-03-19 improved the user manuals
2020-03-20 ml/index.rst translated
2020-03-20 some malayalam RST files modified
2020-03-20 changes to let Xelatex compile the static PDF files
2020-03-20 enforced an upper width for pictures : 400px
2020-03-21 edited preface
2020-03-21 1.x.rst files edited
2020-03-21 listed dependencies
2020-03-21 made the background change instantaneous
2020-03-22 added export image option(png, svg). tested with oscilloscope UI. Will not work with experiments where scope does not use a plot called self.pwin (advanced data logger, i2c logger etc)
2020-03-22 added translations for new features for screenshots
2020-03-22 new feature: translate SVG snapshots
2020-03-22 added a way to manage screenshot translation from English to other supported languages
2020-04-03 updated line numbers
2020-04-04 added some comments
2020-04-04 finalized the file writer
2020-04-04 added a new feature: when one makes a screenshot with a dark background, SVG files for print (with a light background) are created along the translations
2020-04-04 the default path for translations is based on the path for the screenshot if not defined previously
2020-04-04 changed the way to do small screenshots (alt-p)
2020-04-04 added options for PNG screenshots
2020-04-04 added PNG screenshots as a spinoff from translations and enligntenments
2020-04-04 restored the credits files
2020-04-05 added the feature for a credits window in eyes-junior
2020-05-01 gu.ts, ta.ts added
2020-05-05 more language files and help directories added menu shows language names
2020-05-05 calculate statistics of localization
2020-05-06 created a more powerful Language class
2020-05-06 separated the Language class in another file
2020-05-06 updated translations
2020-05-06 create missing flags
2020-05-06 the normalised name for Bengali is bn
2020-05-07 mad the docstring more precise for createFlagStatus
2020-05-07 removed the unused variable langNames
2020-05-08 .ts files edited
2020-05-12 tamil translation added. Corrected some typos.
2020-05-15 udpated ts files with pylupdate
2020-05-15 make an absolute directory in the path
2020-07-24 fixed the export of SVG screenshots with weird matrix transforms
2020-07-25 fixed the weird with for screenshots got with Alt-P, also
2020-07-25 first step for a screenshot service
2020-07-25 screenshot web service OK for SVG (full and small)
2020-07-25 removed dead code
2020-07-26 fix the matrix problem for all paths, not only traces of the oscilloscope
2020-07-26 improved the server's response
2020-07-26 first successful attempt to insert a SVG file
2020-07-27 the macro for LibreOffice is OK; now it misses the possibility to choose parameters
2020-07-27 first stable version of the plugin for LibreOffice
2020-07-27 began to reorganize the files like those of APSO
2020-07-27 some fuzzy tries
2020-07-28 reorganised the plugin for an installation by a debian package
2020-07-28 .ps files added transistor, res-phase
2020-07-28 added descriptions and images
2020-07-28 added meta informations
2020-07-29 schematics added to scircuit directory
2020-07-29 improved the socket service for web browsers
2020-07-29 updated l10n
2020-07-31 fixed non-ascii characters in math expressions
2020-07-31 files */rst/exp/Makefile are now generated files
2020-07-31 restored missing pdf cover pages
2020-07-31 updated user manuals
2020-08-01 mofified the Makefile to use XeLaTeX
2020-08-01 updated tex file preprocessors
2020-08-01 use $(MAKE) instead of make -j4
2020-08-01 parallelized better the makefile
2020-08-01 yet another improvement with a cache for generated PDF images
2020-08-08 publish files made by rst2html
2020-08-08 fixed some paths
2020-08-08 updated language files
2020-08-08 fixed the makefile for kuttypy firmware
2020-08-09 new development with wxglade
2020-08-09 moved new files around
2020-08-09 graphic interface almost complete
2020-08-09 the editor can be used
2020-08-09 made 'file new' more robust
2020-08-10 first success for a syntax highlighting
2020-08-11 added a series of examples
2020-08-11 implemented the file->init() procedure, improved the closing check-up
2020-08-11 improved the management of file names and file saving
2020-08-17 fixed font references for Linux
2020-08-17 fixed the hardware detection
2020-08-17 removed the menu to change font size, since it is possible by wheeling with the mouse
2020-08-17 simplified the code for zoomin/zoomout keyboard shortcuts
2020-08-17 implemented black on white and the reverse callback
2020-08-18 simplified the construction of paths
2020-08-18 Build -> Upload implemented
2020-08-18 Upload bootloader implemented
2020-08-18 implemented the actions for About menu
2020-08-18 inluded copyright information
2020-08-18 ported the French translation from uhope.c and mh-ide.py
2020-08-18 updated the translations
2020-08-18 modified the Makefile to take in account only the latest microhope.py/ uhope development
2020-08-20 defined a new location for the local microhope directory: ~/.local/share/microhope
2020-08-20 take in account the directory uhope/
2020-08-20 ignore no longer html documentation files
2020-08-21 restored the feature to have a microhope environment visible in the home directory
2020-08-21 added a configuration file, managed by configparser
2021-03-23 minor modifications to advancedLogger
2021-07-01 new version 4.8.8
2022-03-19 fixed the Makefile
2022-03-20 use img2pdf instead of convert to make temporary PDF
2022-03-20 modified --section-start=.text=0x7300 instead of 0x7800
2022-03-20 simple update due to « make »
2022-03-25 improved Makefiles Makefile bin/Makefile
2022-03-26 improved the installation's target
2022-03-26 refreshed translations
2022-03-26 fixed eyes17's layouts installation
2022-07-17 changes to support Qt6 (only version of Qt supported from now on
2022-07-17 removed broken symlinks
2022-07-19 replaced :width: by :figwidth: in a Figure
2022-07-19 removed generated files
2022-07-19 fixed a figure
2022-07-19 improvd the clean target
2022-07-19 fixed references of images
2022-07-19 replace unicode "×" by \times"
2022-07-20 came back from wildcard to shell directive, as there were pipes in the command
2022-07-20 defined targets override_dh_auto_install-indep and override_dh_auto_install-arch
2022-07-21 add a book cover to e-books
2022-07-21 now e-books have a cover page
2022-07-21 fixed the type Qt.AlignmentFlag
2022-07-21 ensure val is converted to a string before setText
2022-07-21 use logging to get more insight about errors in imported modules
2022-07-21 fixed Qt.Horizontal
2022-07-21 fixed Qt.AlignLeft
2022-07-21 fixed QShortcut issues
2022-07-21 fixed QFont.Bold
2022-07-21 fixed QRegRxp
2022-07-21 fixed indexIn
2022-07-22 introduced QRegularExpression
2022-07-22 first reimplementation of regexp parsing
2022-07-22 updated dependencies
2022-07-22 still trying to deal with multiline comments
2022-07-22 fixed the table
2022-07-22 remove the dependency on img2pdf
2022-07-22 | img2pdf | 0.4.4-2 | all | Lossless conversion of raster images to PDF |
2022-08-23 first publication
2022-08-23 changed the debian packaging files
2022-08-23 modified Makefile to take the file build_eyes17_only in account
2022-08-23 fixed paths
2022-08-23 do not install rst files
2022-08-23 consider eyes17 only with setup.py
2022-08-23 removed make targets which are useless for eyes17
2022-08-24 res files
2022-08-26 final pyqt5
2022-08-27 modify makefile to add Blockly folder to eyes17 package
2022-08-27 defined LANG=C for pylupdate5 to do its work properly
2022-08-27 defined LANG as en_US.UTF-8
2022-09-16 major changes to block interface
2022-09-27 handle disconnect and reconnect events
2022-10-01 fixed the syntax for defining a variable's value
2022-10-01 try to merge
2022-10-01 added a command to view eyes17's manuals
2022-10-01 modified the desktop file for eyes17's user manual
2022-10-21 add simulator for testing
2022-10-26 fix translation files merge error
2022-11-14 add multiplexed logger
2022-11-14 fixed eyes17's manuals references and reader
2022-11-15 modified the desktop file for eyes17-manuals
2022-11-28 deleted debian/compat
2022-11-28 new version number
2022-11-28 modified the ignore policy
2022-11-28 fixed a duplication
2022-11-28 separated eyes17 and the plugin for blockly
2022-11-28 separate blockly from eyes17
2022-11-28 defined a warning message when blockly is missing
2022-12-15 recreate helpwin on deselect/select help checkbox. previously the helpwin would not re-show after being hidden
    show err if capacitance <1pF
    save data function added for multiplexed logger
    multiplexed logger. add msg label
2023-10-05 change code examples to replace pylab with matplotlib.pyplot. try different paths for configparser module
2023-10-15 create docs for library using mkdocs
2023-11-05 use gm convert instead of img2pdf and convert
2023-11-05 updated a translation file
2024-04-16 added sensor oscilloscope. https://csparkresearch.in/expeyes17/sensors/sensor-scope.html
2024-12-03 fix debian bug #1088452: expeyes-web: move from twitter-bootstrap{3,4} to bootstrap-html (v5)
2025-04-02 initiated a Breton translation file from the French one
2025-10-04 new icon for microhope-doc's desktop file
2025-10-04 python is python3 now
